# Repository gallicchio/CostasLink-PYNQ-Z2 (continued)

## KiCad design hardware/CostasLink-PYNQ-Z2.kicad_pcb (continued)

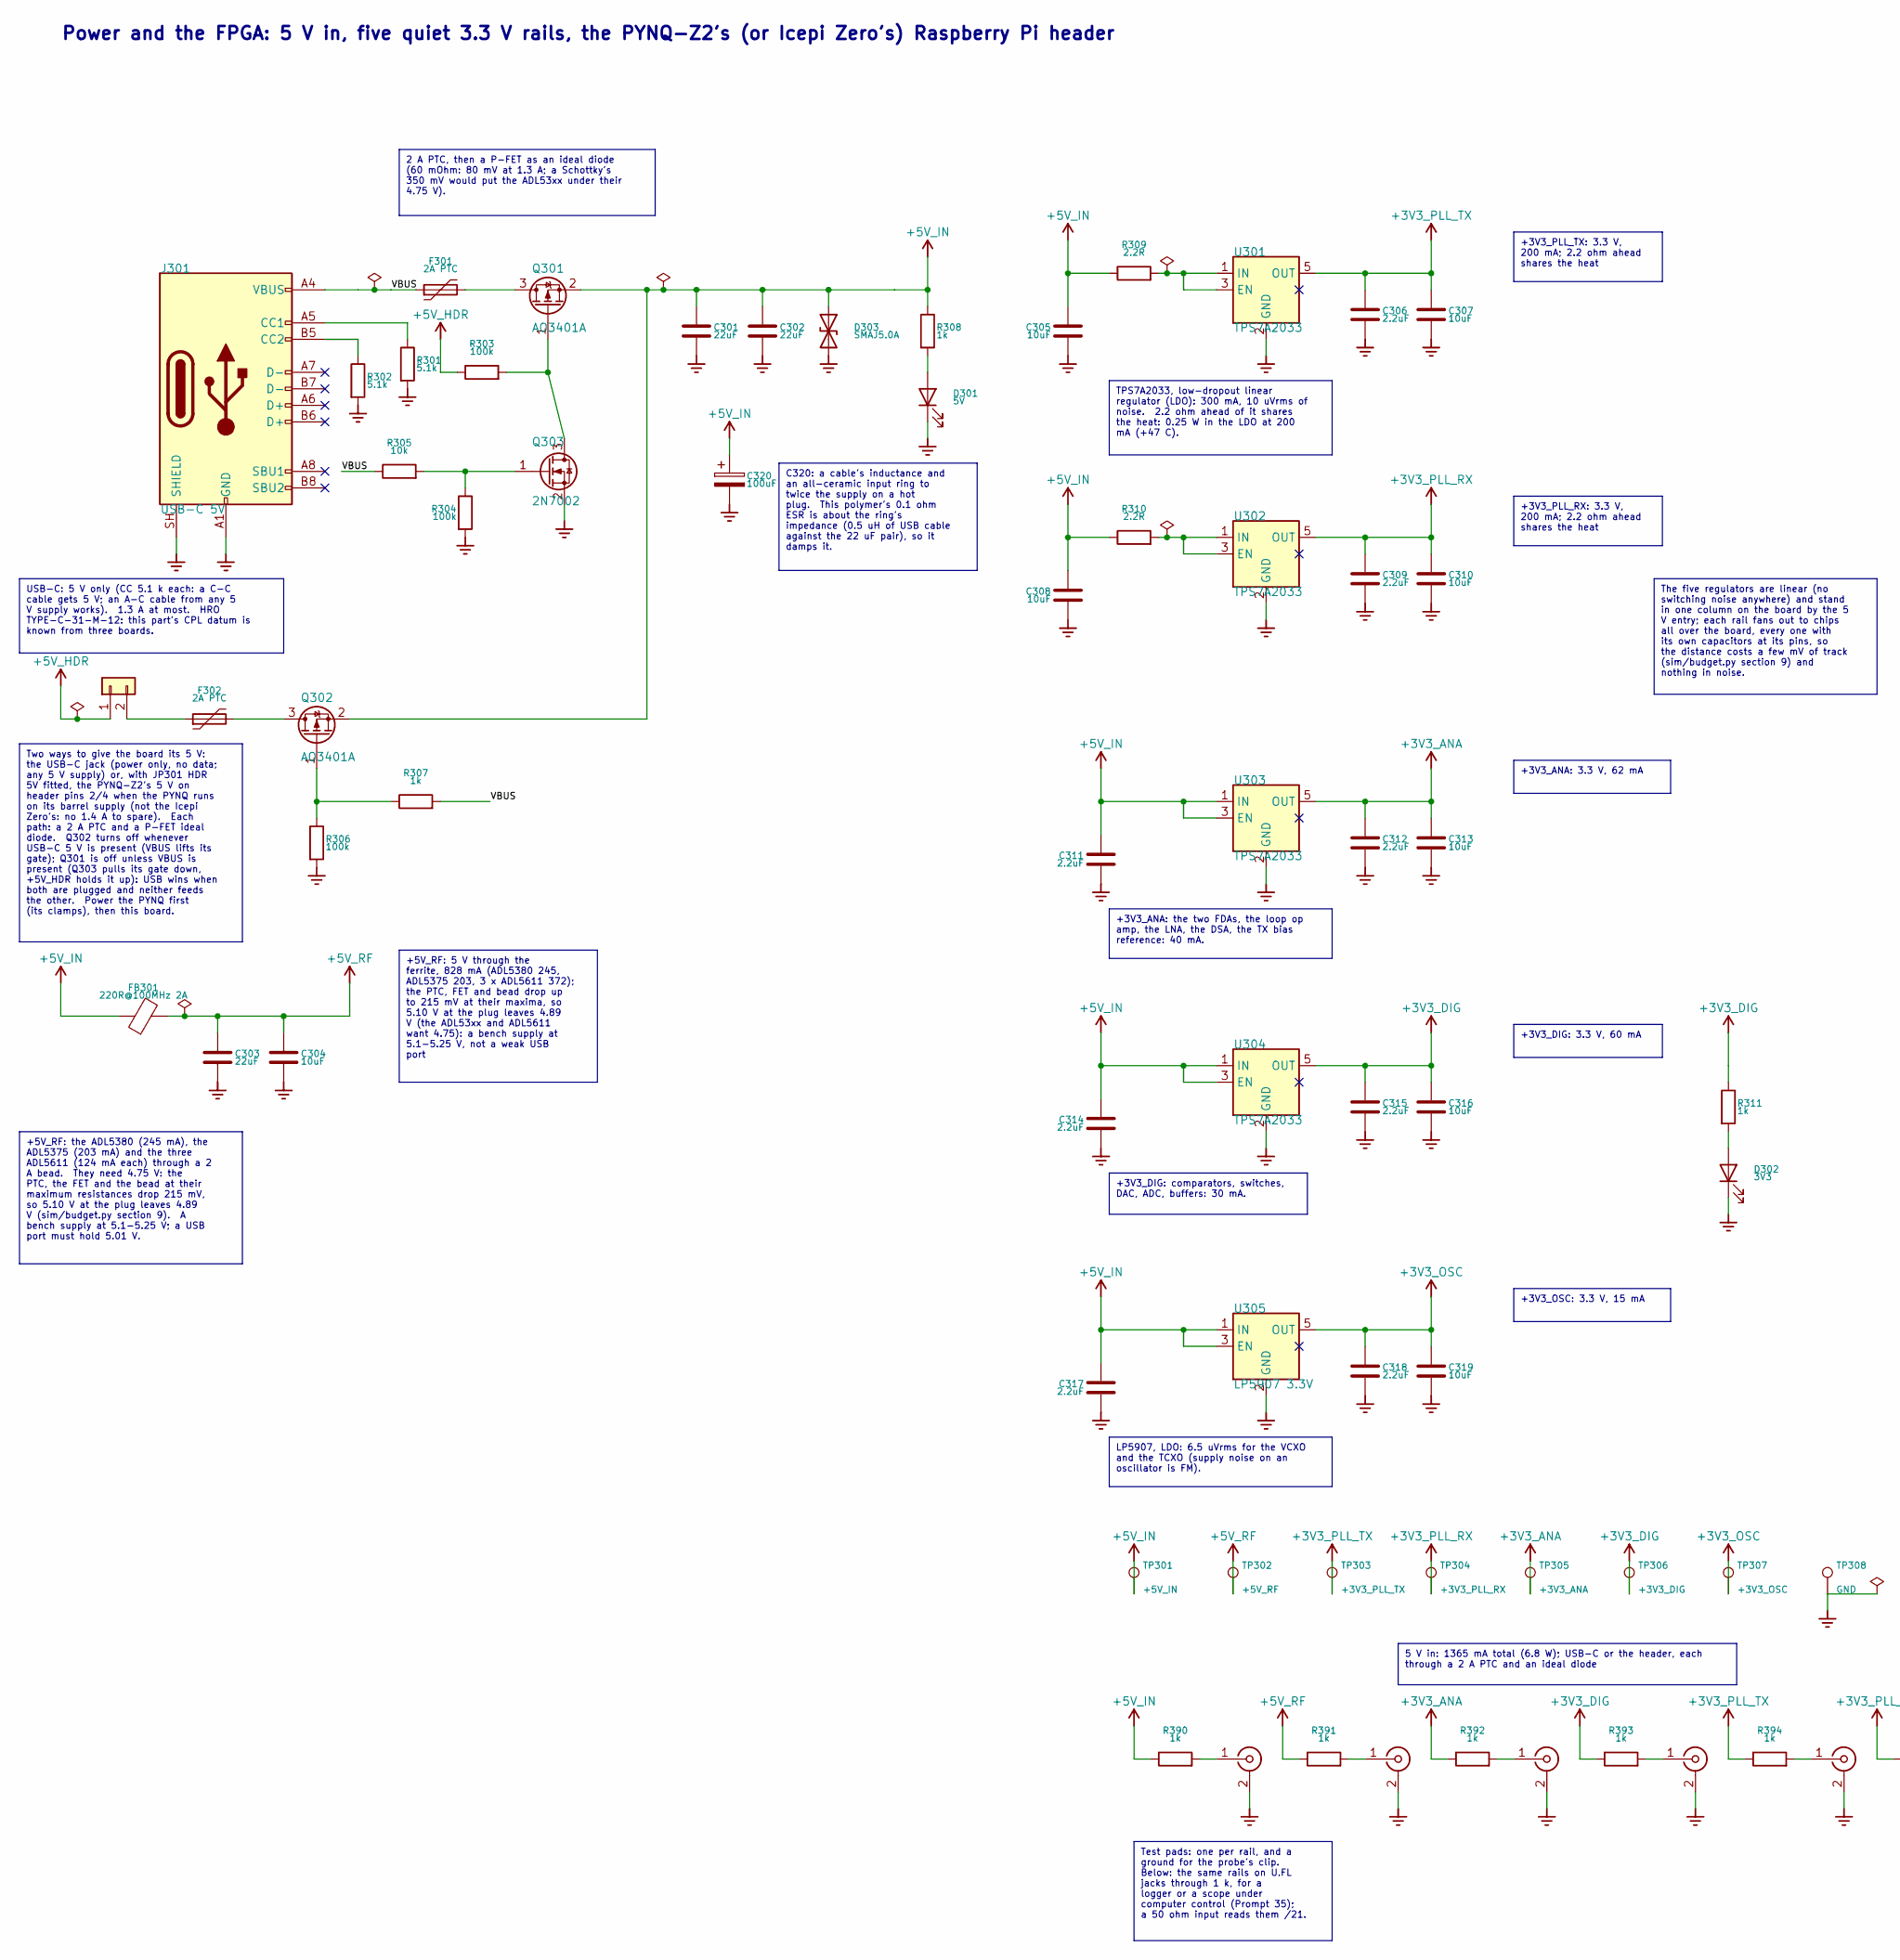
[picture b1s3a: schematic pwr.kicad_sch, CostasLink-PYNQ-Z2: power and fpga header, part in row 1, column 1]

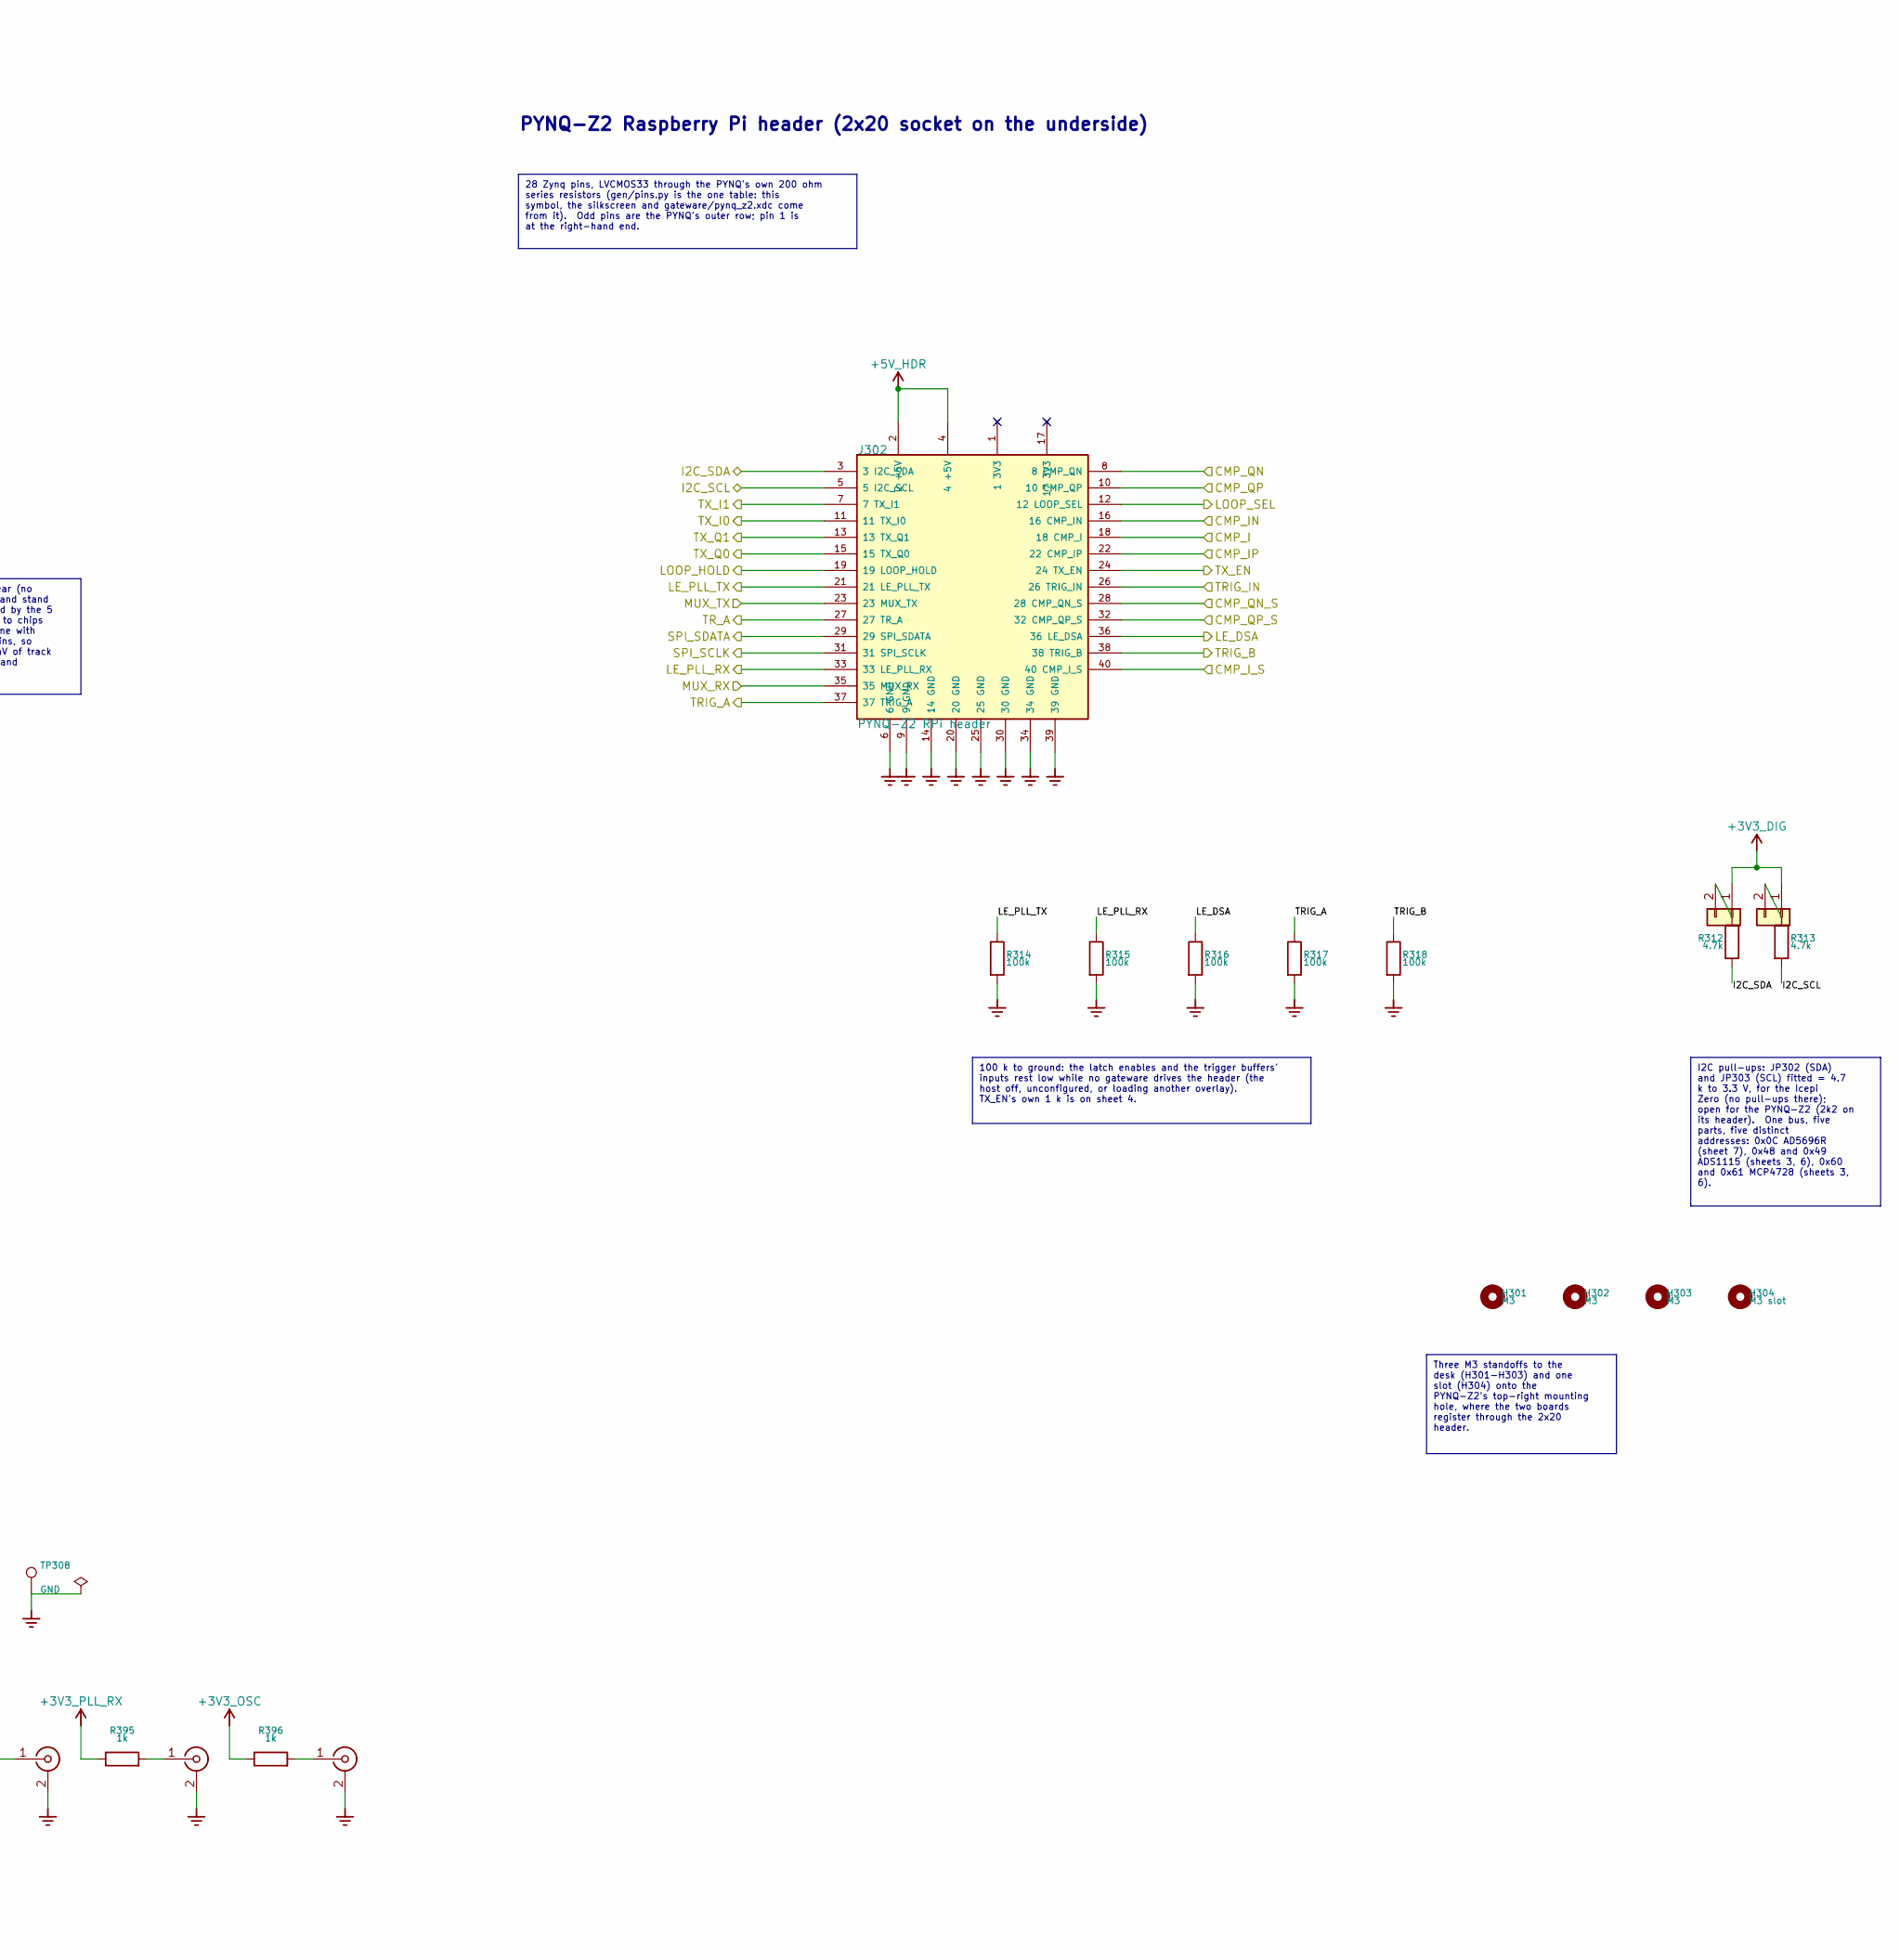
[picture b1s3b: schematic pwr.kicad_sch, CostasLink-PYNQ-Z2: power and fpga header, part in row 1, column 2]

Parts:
C301, C302, C303: 22uF; C_0805_2012Metric; MPN CL21A226MAQNNNE; LCSC C45783
C304, C305, C307, C308, C310, C313, C316, C319: 10uF; C_0805_2012Metric; MPN CL21A106KAYNNNE; LCSC C15850
C306, C309, C311, C312, C314, C315, C317, C318: 2.2uF; C_0603_1608Metric; MPN CL10A225KO8NNNC; LCSC C23630
C320: 100uF; CP_Elec_5x5.9; MPN 1010100506TR; LCSC C19270534
D301: 5V; LED_0603_1608Metric; MPN KT-0603R; LCSC C2286
D302: 3V3; LED_0603_1608Metric; MPN KT-0603R; LCSC C2286
D303: SMAJ5.0A; D_SMA; MPN SMAJ5.0A; LCSC C113952
F301, F302: 2A PTC; Fuse_1812_4532Metric; MPN MF-MSMF200-2; LCSC C210837
FB301: 220R@100MHz 2A; L_0805_2012Metric; MPN BLM21PG221SN1D; LCSC C85840
H301, H302, H303: M3; MountingHole_3.2mm_M3_DIN965
H304: M3 slot; MountingHole_Slot_3.2x5.2mm_M3
J301: USB-C 5V; USB_C_Receptacle_HRO_TYPE-C-31-M-12; MPN TYPE-C-31-M-12; LCSC C165948
J302: PYNQ-Z2 RPi header; RPi_Socket_2x20_P2.54mm_Underside; MPN 2.54-2*20; LCSC C2977589
J390: 5V_IN; U.FL_Hirose_U.FL-R-SMT-1_Vertical; MPN U.FL-R-SMT-1(80); LCSC C88374
J391: 5V_RF; U.FL_Hirose_U.FL-R-SMT-1_Vertical; MPN U.FL-R-SMT-1(80); LCSC C88374
J392: 3V3_ANA; U.FL_Hirose_U.FL-R-SMT-1_Vertical; MPN U.FL-R-SMT-1(80); LCSC C88374
J393: 3V3_DIG; U.FL_Hirose_U.FL-R-SMT-1_Vertical; MPN U.FL-R-SMT-1(80); LCSC C88374
J394: 3V3_PLL_TX; U.FL_Hirose_U.FL-R-SMT-1_Vertical; MPN U.FL-R-SMT-1(80); LCSC C88374
J395: 3V3_PLL_RX; U.FL_Hirose_U.FL-R-SMT-1_Vertical; MPN U.FL-R-SMT-1(80); LCSC C88374
J396: 3V3_OSC; U.FL_Hirose_U.FL-R-SMT-1_Vertical; MPN U.FL-R-SMT-1(80); LCSC C88374
JP301: HDR 5V; PinHeader_1x02_P2.54mm_Vertical; MPN PZ254V-11-02P; LCSC C492401
JP302: SDA PU; PinHeader_1x02_P2.54mm_Vertical; MPN PZ254V-11-02P; LCSC C492401
JP303: SCL PU; PinHeader_1x02_P2.54mm_Vertical; MPN PZ254V-11-02P; LCSC C492401
Q301, Q302: AO3401A; SOT-23; MPN AO3401A; LCSC C15127
Q303: 2N7002; SOT-23; MPN 2N7002; LCSC C8545
R301, R302: 5.1k; R_0402_1005Metric; MPN 0402WGF5101TCE; LCSC C25905
R303, R304, R306, R314, R315, R316, R317, R318: 100k; R_0402_1005Metric; MPN 0402WGF1003TCE; LCSC C25741
R305: 10k; R_0402_1005Metric; MPN 0402WGF1002TCE; LCSC C25744
R307, R308, R311, R390, R391, R392, R393, R394, R395, R396: 1k; R_0402_1005Metric; MPN 0402WGF1001TCE; LCSC C11702
R309, R310: 2.2R; R_1206_3216Metric; MPN AC1206FR-072R2L; LCSC C144499
R312, R313: 4.7k; R_0402_1005Metric; MPN 0402WGF4701TCE; LCSC C25900
TP301: +5V_IN; TestPoint_Pad_D1.5mm
TP302: +5V_RF; TestPoint_Pad_D1.5mm
TP303: +3V3_PLL_TX; TestPoint_Pad_D1.5mm
TP304: +3V3_PLL_RX; TestPoint_Pad_D1.5mm
TP305: +3V3_ANA; TestPoint_Pad_D1.5mm
TP306: +3V3_DIG; TestPoint_Pad_D1.5mm
TP307: +3V3_OSC; TestPoint_Pad_D1.5mm
TP308: GND; TestPoint_Pad_D1.5mm
U301, U302, U303, U304: TPS7A2033; SOT-23-5; MPN TPS7A2033PDBVR; LCSC C2862740
U305: LP5907 3.3V; SOT-23-5; MPN LP5907MFX-3.3; LCSC C23380874

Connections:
+3V3_ANA: C312.1, C313.1, R392.1, TP305.1, U303.5 (OUT); also elsewhere on the board
+3V3_DIG: C315.1, C316.1, JP302.1, JP302.2, JP303.1, JP303.2, R311.1, R312.1, R313.1, R393.1, TP306.1, U304.5 (OUT); also elsewhere on the board
+3V3_OSC: C318.1, C319.1, R396.1, TP307.1, U305.5 (OUT); also elsewhere on the board
+3V3_PLL_RX: C309.1, C310.1, R395.1, TP304.1, U302.5 (OUT); also elsewhere on the board
+3V3_PLL_TX: C306.1, C307.1, R394.1, TP303.1, U301.5 (OUT); also elsewhere on the board
+5V_HDR: J302.2 (2 +5V), J302.4 (4 +5V), JP301.1, R303.1
+5V_IN: C301.1, C302.1, C305.1, C308.1, C311.1, C314.1, C317.1, C320.1, D303.1 (A1), FB301.1, Q301.2 (S), Q302.2 (S), R308.1, R309.1, R310.1, R390.1, TP301.1, U303.1 (IN), U303.3 (EN), U304.1 (IN), U304.3 (EN), U305.1 (IN), U305.3 (EN)
+5V_RF: C303.1, C304.1, FB301.2, R391.1, TP302.1; also elsewhere on the board
/Antenna switch: one antenna by T/R/TR_A: J302.27 (27 TR_A); also elsewhere on the board
/CMP_IN: J302.16 (16 CMP_IN); also elsewhere on the board
/CMP_IP: J302.22 (22 CMP_IP); also elsewhere on the board
/CMP_QN: J302.8 (8 CMP_QN); also elsewhere on the board
/CMP_QP: J302.10 (10 CMP_QP); also elsewhere on the board
/I2C_SCL: J302.5 (5 I2C_SCL), R313.2; also elsewhere on the board
/I2C_SDA: J302.3 (3 I2C_SDA), R312.2; also elsewhere on the board
/Power and FPGA header/CMP_I_S: J302.40 (40 CMP_I_S); also elsewhere on the board
/Power and FPGA header/CMP_QN_S: J302.28 (28 CMP_QN_S); also elsewhere on the board
/Power and FPGA header/CMP_QP_S: J302.32 (32 CMP_QP_S); also elsewhere on the board
/Power and FPGA header/LE_DSA: J302.36 (36 LE_DSA), R316.1; also elsewhere on the board
/Power and FPGA header/LE_PLL_RX: J302.33 (33 LE_PLL_RX), R315.1; also elsewhere on the board
/Power and FPGA header/LE_PLL_TX: J302.21 (21 LE_PLL_TX), R314.1; also elsewhere on the board
/Power and FPGA header/LOOP_HOLD: J302.19 (19 LOOP_HOLD); also elsewhere on the board
/Power and FPGA header/LOOP_SEL: J302.12 (12 LOOP_SEL); also elsewhere on the board
/Power and FPGA header/MUX_RX: J302.35 (35 MUX_RX); also elsewhere on the board
/Power and FPGA header/MUX_TX: J302.23 (23 MUX_TX); also elsewhere on the board
/Power and FPGA header/SPI_SCLK: J302.31 (31 SPI_SCLK); also elsewhere on the board
/Power and FPGA header/SPI_SDATA: J302.29 (29 SPI_SDATA); also elsewhere on the board
/Power and FPGA header/TRIG_A: J302.37 (37 TRIG_A), R317.1; also elsewhere on the board
/Power and FPGA header/TRIG_B: J302.38 (38 TRIG_B), R318.1; also elsewhere on the board
/Power and FPGA header/TX_EN: J302.24 (24 TX_EN); also elsewhere on the board
/Power and FPGA header/TX_I0: J302.11 (11 TX_I0); also elsewhere on the board
/Power and FPGA header/TX_I1: J302.7 (7 TX_I1); also elsewhere on the board
/Power and FPGA header/TX_Q0: J302.15 (15 TX_Q0); also elsewhere on the board
/Power and FPGA header/VBUS: F301.1, J301.A4 (VBUS), J301.A9 (VBUS), J301.B4 (VBUS), J301.B9 (VBUS), R305.1, R307.2
/Receiver and Costas loop/CMP_I: J302.18 (18 CMP_I); also elsewhere on the board
unnamed: D301.2 (A), R308.2
unnamed: D302.2 (A), R311.2
unnamed: J301.A5 (CC1), R301.1
unnamed: J301.B5 (CC2), R302.1
unnamed: J390.1 (In), R390.2
unnamed: J391.1 (In), R391.2
unnamed: J392.1 (In), R392.2
unnamed: J393.1 (In), R393.2
unnamed: J394.1 (In), R394.2
unnamed: J395.1 (In), R395.2
unnamed: J396.1 (In), R396.2
unnamed: F302.1, JP301.2
unnamed: F301.2, Q301.3 (D)
unnamed: Q301.1 (G), Q303.3 (D), R303.2
unnamed: F302.2, Q302.3 (D)
unnamed: Q302.1 (G), R306.1, R307.1
unnamed: Q303.1 (G), R304.1, R305.2
unnamed: R309.2, U301.1 (IN), U301.3 (EN)
unnamed: R310.2, U302.1 (IN), U302.3 (EN)

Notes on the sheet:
Power and the FPGA: 5 V in, five quiet 3.3 V rails, the PYNQ-Z2's (or Icepi Zero's) Raspberry Pi header
PYNQ-Z2 Raspberry Pi header (2x20 socket on the underside)
USB-C: 5 V only (CC 5.1 k each: a C-C cable gets 5 V; an A-C cable from any 5 V supply works). 1.3 A at most. HRO TYPE-C-31-M-12: this part's CPL datum is known from three boards.
2 A PTC, then a P-FET as an ideal diode (60 mOhm: 80 mV at 1.3 A; a Schottky's 350 mV would put the ADL53xx under their 4.75 V).
Two ways to give the board its 5 V: the USB-C jack (power only, no data; any 5 V supply) or, with JP301 HDR 5V fitted, the PYNQ-Z2's 5 V on header pins 2/4 when the PYNQ runs on its barrel supply (not the Icepi Zero's: no 1.4 A to spare). Each path: a 2 A PTC and a P-FET ideal diode. Q302 turns off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
C320: a cable's inductance and an all-ceramic input ring to twice the supply on a hot plug. This polymer's 0.1 ohm ESR is about the ring's impedance (0.5 uH of USB cable against the 22 uF pair), so it damps it.
+5V_RF: 5 V through the ferrite, 828 mA (ADL5380 245, ADL5375 203, 3 x ADL5611 372); the PTC, FET and bead drop up to 215 mV at their maxima, so 5.10 V at the plug leaves 4.89 V (the ADL53xx and ADL5611 want 4.75): a bench supply at 5.1-5.25 V, not a weak USB port
+5V_RF: the ADL5380 (245 mA), the ADL5375 (203 mA) and the three ADL5611 (124 mA each) through a 2 A bead. They need 4.75 V: the PTC, the FET and the bead at their maximum resistances drop 215 mV, so 5.10 V at the plug leaves 4.89 V (sim/budget.py section 9). A bench supply at 5.1-5.25 V; a USB por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
+3V3_PLL_TX: 3.3 V, 200 mA; 2.2 ohm ahead shares the heat
TPS7A2033, low-dropout linear regulator (LDO): 300 mA, 10 uVrms of noise. 2.2 ohm ahead of it shares the heat: 0.25 W in the LDO at 200 mA (+47 C).
The five regulators are linear (no switching noise anywhere) and stand in one column on the board by the 5 V entry; each rail fans out to chips all over the board, every one with its own capacitors at its pins, so the distance costs a few mV of track (sim/budget.py section 9) and nothing in noise.
+3V3_PLL_RX: 3.3 V, 200 mA; 2.2 ohm ahead shares the heat
+3V3_ANA: 3.3 V, 62 mA
+3V3_ANA: the two FDAs, the loop op amp, the LNA, the DSA, the TX bias reference: 40 mA.
+3V3_DIG: 3.3 V, 60 mA
+3V3_DIG: comparators, switches, DAC, ADC, buffers: 30 mA.
+3V3_OSC: 3.3 V, 15 mA
LP5907, LDO: 6.5 uVrms for the VCXO and the TCXO (supply noise on an oscillator is FM).
Test pads: one per rail, and a ground for the probe's clip. Below: the same rails on U.FL jacks through 1 k, for a logger or a scope under computer control (Prompt 35); a 50 ohm input reads them /21.
5 V in: 1365 mA total (6.8 W); USB-C or the header, each through a 2 A PTC and an ideal diode
28 Zynq pins, LVCMOS33 through the PYNQ's own 200 ohm series resistors (gen/pins.py is the one table: this symbol, the silkscreen and gateware/pynq_z2.xdc come from it). Odd pins are the PYNQ's outer row; pin 1 is at the right-hand end.
I2C pull-ups: JP302 (SDA) and JP303 (SCL) fitted = 4.7 k to 3.3 V, for the Icepi Zero (no pull-ups there); open for the PYNQ-Z2 (2k2 on its header). One bus, five parts, five distinct addresses: 0x0C AD5696R (sheet 7), 0x48 and 0x49 ADS1115 (sheets 3, 6), 0x60 and 0x61 MCP4728 (sheets 3, 6).
100 k to ground: the latch enables and the trigger buffers' inputs rest low while no gateware drives the header (the host off, unconfigured, or loading another overlay). TX_EN's own 1 k is on sheet 4.
Three M3 standoffs to the desk (H301-H303) and one slot (H304) onto the PYNQ-Z2's top-right mounting hole, where the two boards register through the 2x20 header.

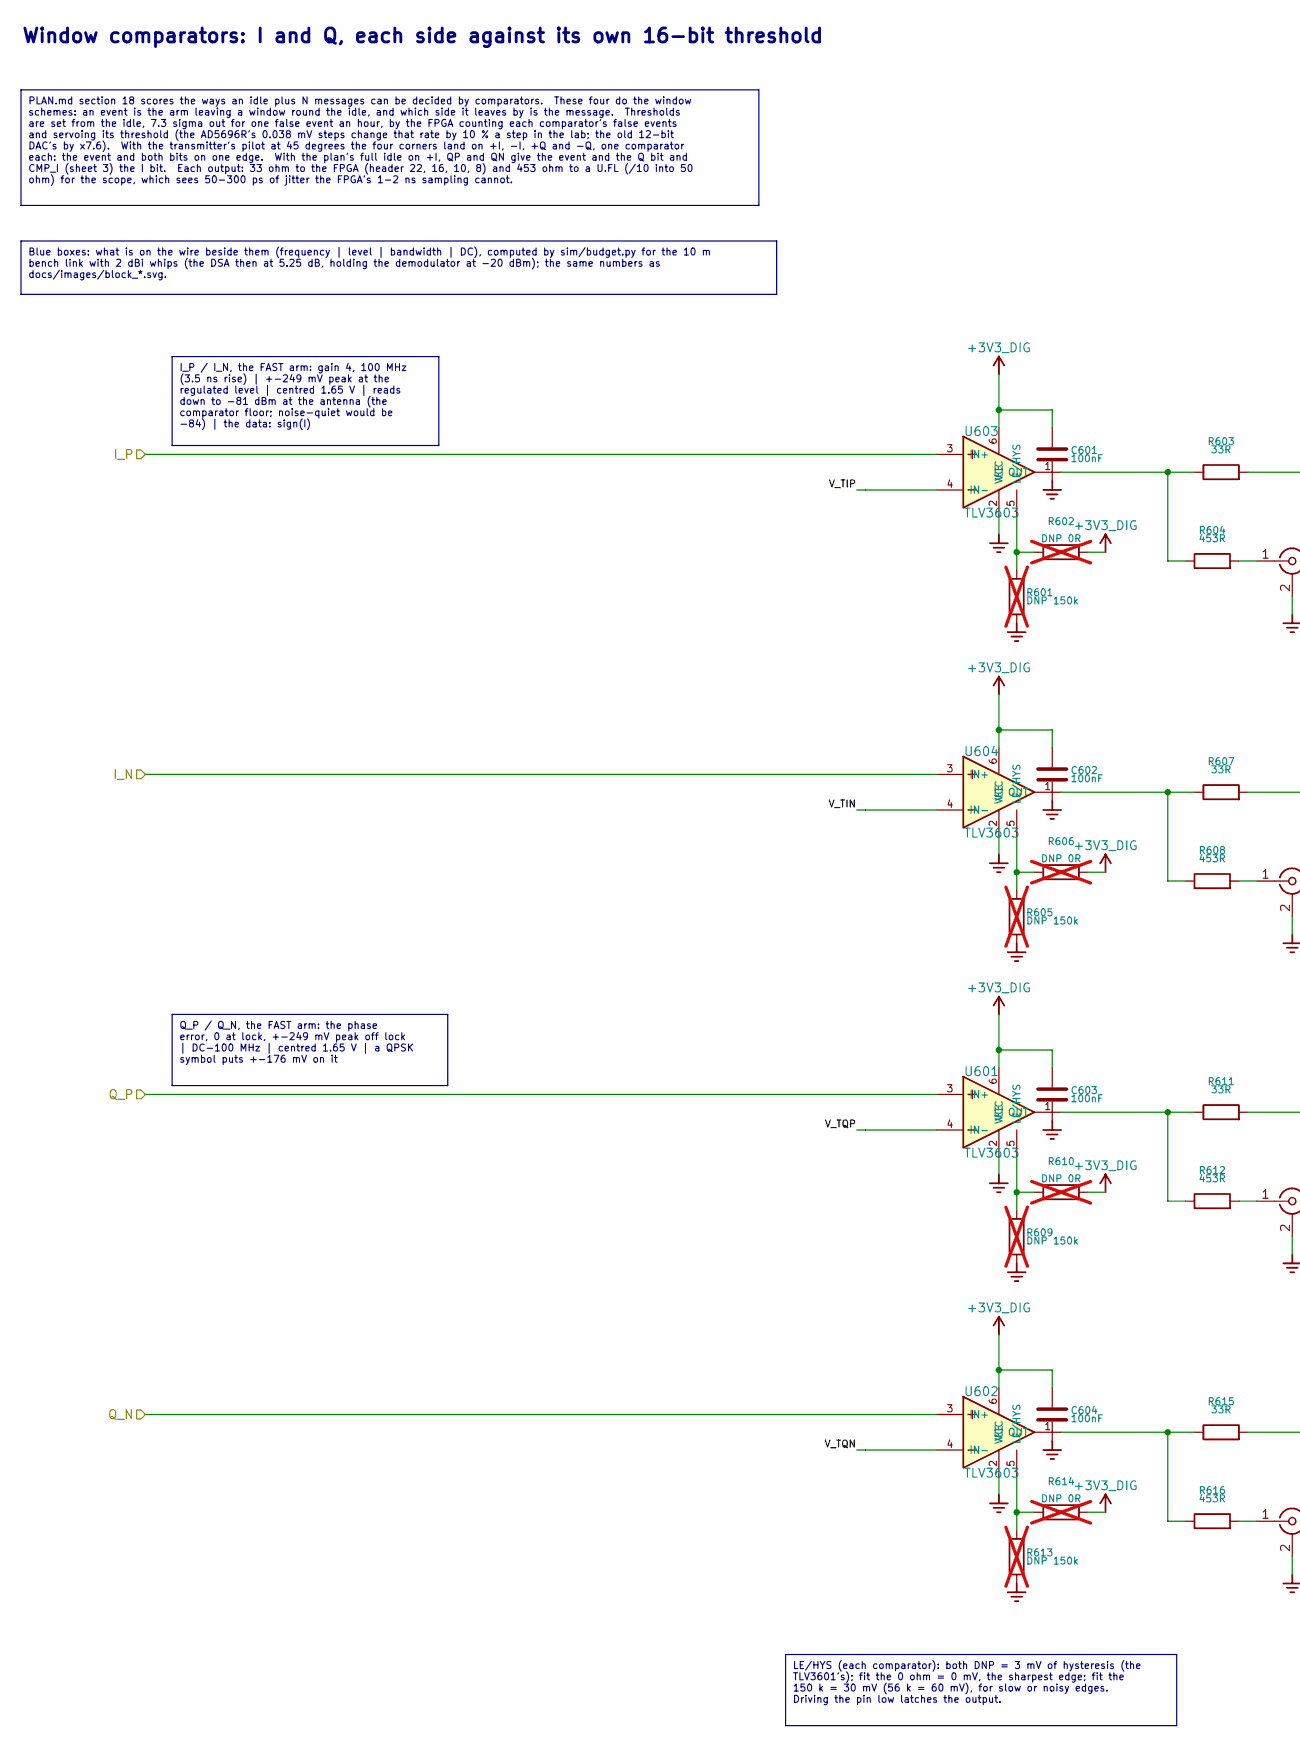
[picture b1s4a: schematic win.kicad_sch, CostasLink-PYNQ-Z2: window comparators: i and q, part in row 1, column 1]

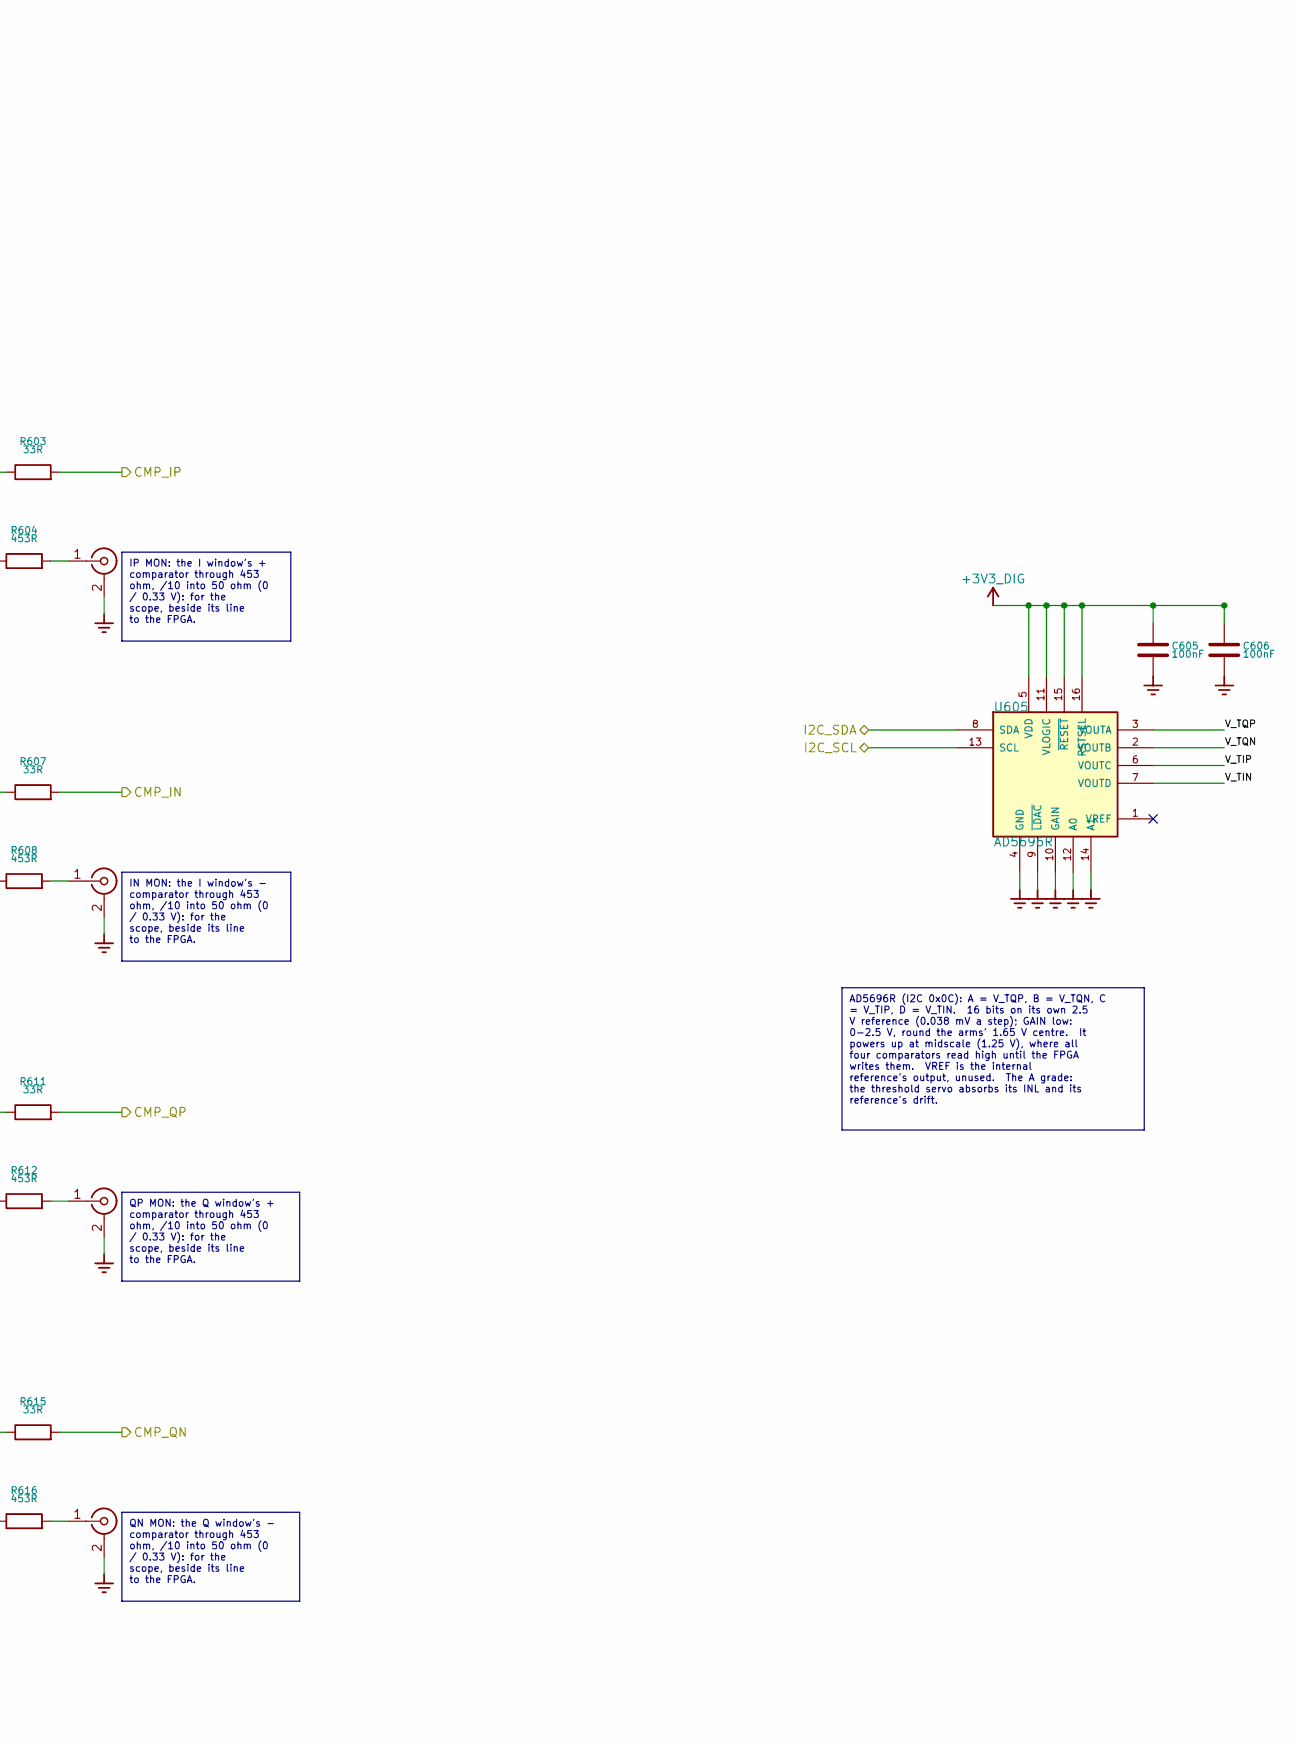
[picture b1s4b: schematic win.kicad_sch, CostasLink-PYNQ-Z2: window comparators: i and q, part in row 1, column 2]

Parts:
C601, C602, C603, C604, C605, C606: 100nF; C_0402_1005Metric; MPN CL05B104KO5NNNC; LCSC C1525
J601: IP MON; U.FL_Hirose_U.FL-R-SMT-1_Vertical; MPN U.FL-R-SMT-1(80); LCSC C88374
J602: IN MON; U.FL_Hirose_U.FL-R-SMT-1_Vertical; MPN U.FL-R-SMT-1(80); LCSC C88374
J603: QP MON; U.FL_Hirose_U.FL-R-SMT-1_Vertical; MPN U.FL-R-SMT-1(80); LCSC C88374
J604: QN MON; U.FL_Hirose_U.FL-R-SMT-1_Vertical; MPN U.FL-R-SMT-1(80); LCSC C88374
R601, R605, R609, R613: DNP 150k; R_0402_1005Metric; MPN 0402WGF1503TCE; LCSC C25755; not fitted
R602, R606, R610, R614: DNP 0R; R_0402_1005Metric; MPN 0402WGF0000TCE; LCSC C17168; not fitted
R603, R607, R611, R615: 33R; R_0402_1005Metric; MPN 0402WGF330JTCE; LCSC C25105
R604, R608, R612, R616: 453R; R_0402_1005Metric; MPN FRC0402F4530TS; LCSC C5126227
U601, U602, U603, U604: TLV3603; SOT-363_SC-70-6; MPN TLV3603DCKR; LCSC C5213955
U605: AD5696R; TSSOP-16_4.4x5mm_P0.65mm; MPN AD5696RARUZ; LCSC C650158

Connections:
+3V3_DIG: C601.1, C602.1, C603.1, C604.1, C605.1, C606.1, R602.2, R606.2, R610.2, R614.2, U601.6 (VCC), U602.6 (VCC), U603.6 (VCC), U604.6 (VCC), U605.5 (VDD), U605.11 (VLOGIC), U605.15 (~RESET), U605.16 (RSTSEL); also elsewhere on the board
/CMP_IN: R607.2; also elsewhere on the board
/CMP_IP: R603.2; also elsewhere on the board
/CMP_QN: R615.2; also elsewhere on the board
/CMP_QP: R611.2; also elsewhere on the board
/I2C_SCL: U605.13 (SCL); also elsewhere on the board
/I2C_SDA: U605.8 (SDA); also elsewhere on the board
/I_N: U604.3 (IN+); also elsewhere on the board
/I_P: U603.3 (IN+); also elsewhere on the board
/Q_N: U602.3 (IN+); also elsewhere on the board
/Q_P: U601.3 (IN+); also elsewhere on the board
/Window comparators: I and Q/V_TIN: U604.4 (IN-), U605.7 (VOUTD)
/Window comparators: I and Q/V_TIP: U603.4 (IN-), U605.6 (VOUTC)
/Window comparators: I and Q/V_TQN: U602.4 (IN-), U605.2 (VOUTB)
/Window comparators: I and Q/V_TQP: U601.4 (IN-), U605.3 (VOUTA)
unnamed: J601.1 (In), R604.2
unnamed: J602.1 (In), R608.2
unnamed: J603.1 (In), R612.2
unnamed: J604.1 (In), R616.2
unnamed: R609.1, R610.1, U601.5 (LE/HYS)
unnamed: R611.1, R612.1, U601.1 (OUT)
unnamed: R613.1, R614.1, U602.5 (LE/HYS)
unnamed: R615.1, R616.1, U602.1 (OUT)
unnamed: R601.1, R602.1, U603.5 (LE/HYS)
unnamed: R603.1, R604.1, U603.1 (OUT)
unnamed: R605.1, R606.1, U604.5 (LE/HYS)
unnamed: R607.1, R608.1, U604.1 (OUT)

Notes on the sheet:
Window comparators: I and Q, each side against its own 16-bit threshold
PLAN.md section 18 scores the ways an idle plus N messages can be decided by comparators. These four do the window schemes: an event is the arm leaving a window round the idle, and which side it leaves by is the message. Thresholds are set from the idle, 7.3 sigma out for one false event an hour, b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
Blue boxes: what is on the wire beside them (frequency | level | bandwidth | DC), computed by sim/budget.py for the 10 m bench link with 2 dBi whips (the DSA then at 5.25 dB, holding the demodulator at -20 dBm); the same numbers as docs/images/block_*.svg.
IP MON: the I window's + comparator through 453 ohm, /10 into 50 ohm (0 / 0.33 V): for the scope, beside its line to the FPGA.
IN MON: the I window's - comparator through 453 ohm, /10 into 50 ohm (0 / 0.33 V): for the scope, beside its line to the FPGA.
QP MON: the Q window's + comparator through 453 ohm, /10 into 50 ohm (0 / 0.33 V): for the scope, beside its line to the FPGA.
QN MON: the Q window's - comparator through 453 ohm, /10 into 50 ohm (0 / 0.33 V): for the scope, beside its line to the FPGA.
I_P / I_N, the FAST arm: gain 4, 100 MHz (3.5 ns rise) | +-249 mV peak at the regulated level | centred 1.65 V | reads down to -81 dBm at the antenna (the comparator floor; noise-quiet would be -84) | the data: sign(I)
Q_P / Q_N, the FAST arm: the phase error, 0 at lock, +-249 mV peak off lock | DC-100 MHz | centred 1.65 V | a QPSK symbol puts +-176 mV on it
LE/HYS (each comparator): both DNP = 3 mV of hysteresis (the TLV3601's); fit the 0 ohm = 0 mV, the sharpest edge; fit the 150 k = 30 mV (56 k = 60 mV), for slow or noisy edges. Driving the pin low latches the output.
AD5696R (I2C 0x0C): A = V_TQP, B = V_TQN, C = V_TIP, D = V_TIN. 16 bits on its own 2.5 V reference (0.038 mV a step); GAIN low: 0-2.5 V, round the arms' 1.65 V centre. It powers up at midscale (1.25 V), where all four comparators read high until the FPGA writes them. VREF is the internal reference'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
